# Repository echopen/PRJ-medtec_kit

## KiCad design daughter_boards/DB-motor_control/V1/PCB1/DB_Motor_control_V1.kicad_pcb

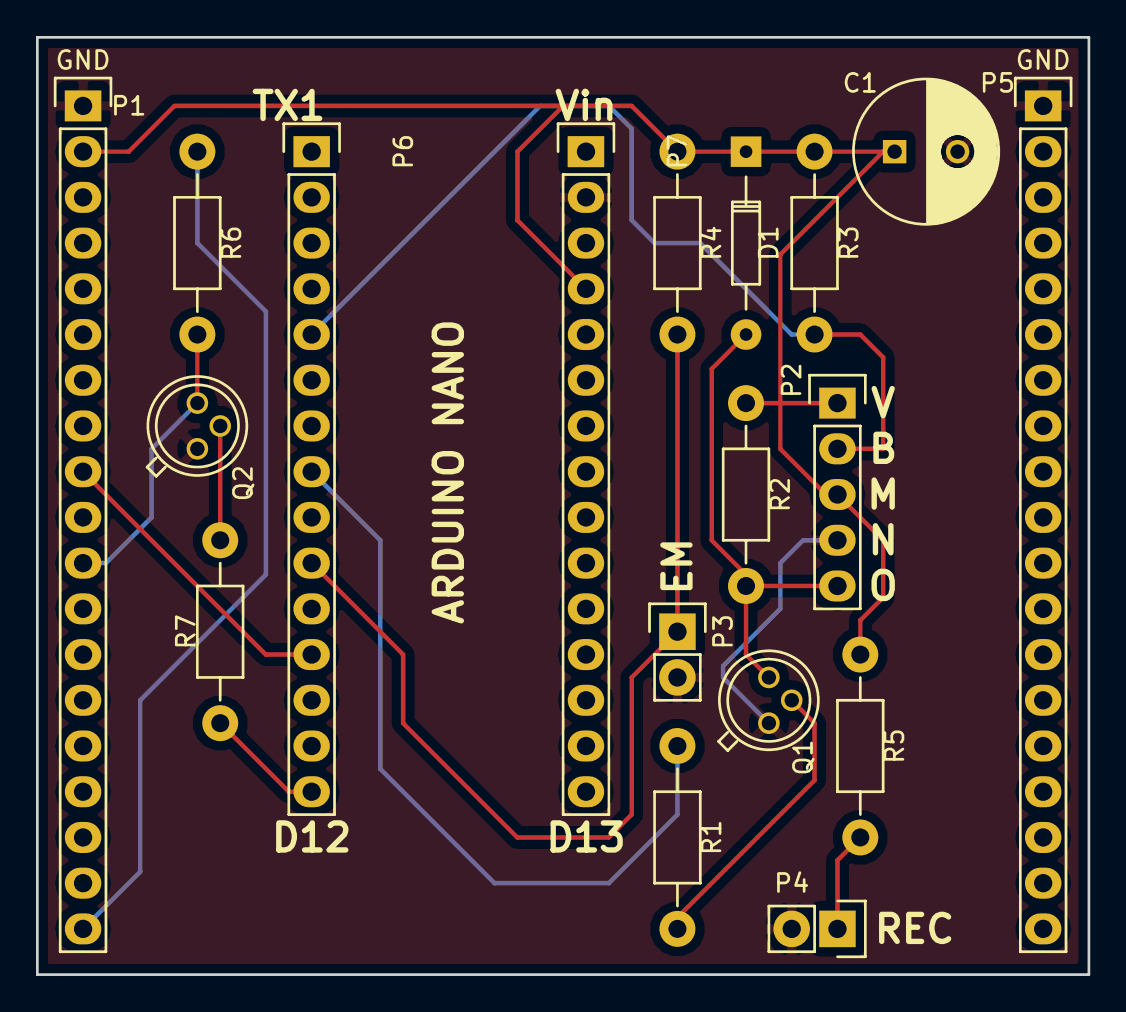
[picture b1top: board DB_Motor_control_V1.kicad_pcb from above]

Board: 2 copper layers, 58.4 x 52.1 mm, 18 parts (0 on the bottom side), 13 nets.

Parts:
C1: 10u; CP_TH_common
D1: 1N4001; Diode_DO-35_SOD27_Horizontal_RM10
P1, P5: CONN_01X19; Header_pin_1x19
P2: CONN_01X05; Socket_Strip_Straight_1x05
P3, P4: CONN_01X02; Socket_Strip_Straight_1x02
P6, P7: CONN_01X15; Socket_Strip_Straight_1x15
Q1: 2N2222; TO-18_3Pin
Q2: 2N2222; TO-18_TH_common
R1: 680; Resistor_Horizontal_RM10mm
R2: 1k; Resistor_Horizontal_RM10mm
R3: 33k; Resistor_Horizontal_RM10mm
R4: 2.2k; Resistor_Horizontal_RM10mm
R5: 330; Resistor_Horizontal_RM10mm
R6, R7: 1.5k; Resistor_TH_common

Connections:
GND: C1.2, P1.1, P2.4, P3.2, P4.2, P5.1, P7.2, Q1.1, Q2.1
unnamed: C1.1, D1.1, P1.2, P2.1, P2.3, P7.4, R2.1, R3.2, R4.1, R5.1
unnamed: D1.2, P2.5, Q1.3, R2.2
unnamed: P1.9, P6.12
unnamed: P1.11, Q2.3, R6.2
unnamed: P1.19, R6.1
unnamed: P2.2, P6.5, R3.1
unnamed: P3.1, P6.10, R4.2
unnamed: P4.1, R5.2
unnamed: P6.8, R1.2
unnamed: P6.15, R7.1
unnamed: Q1.2, R1.1
unnamed: Q2.2, R7.2

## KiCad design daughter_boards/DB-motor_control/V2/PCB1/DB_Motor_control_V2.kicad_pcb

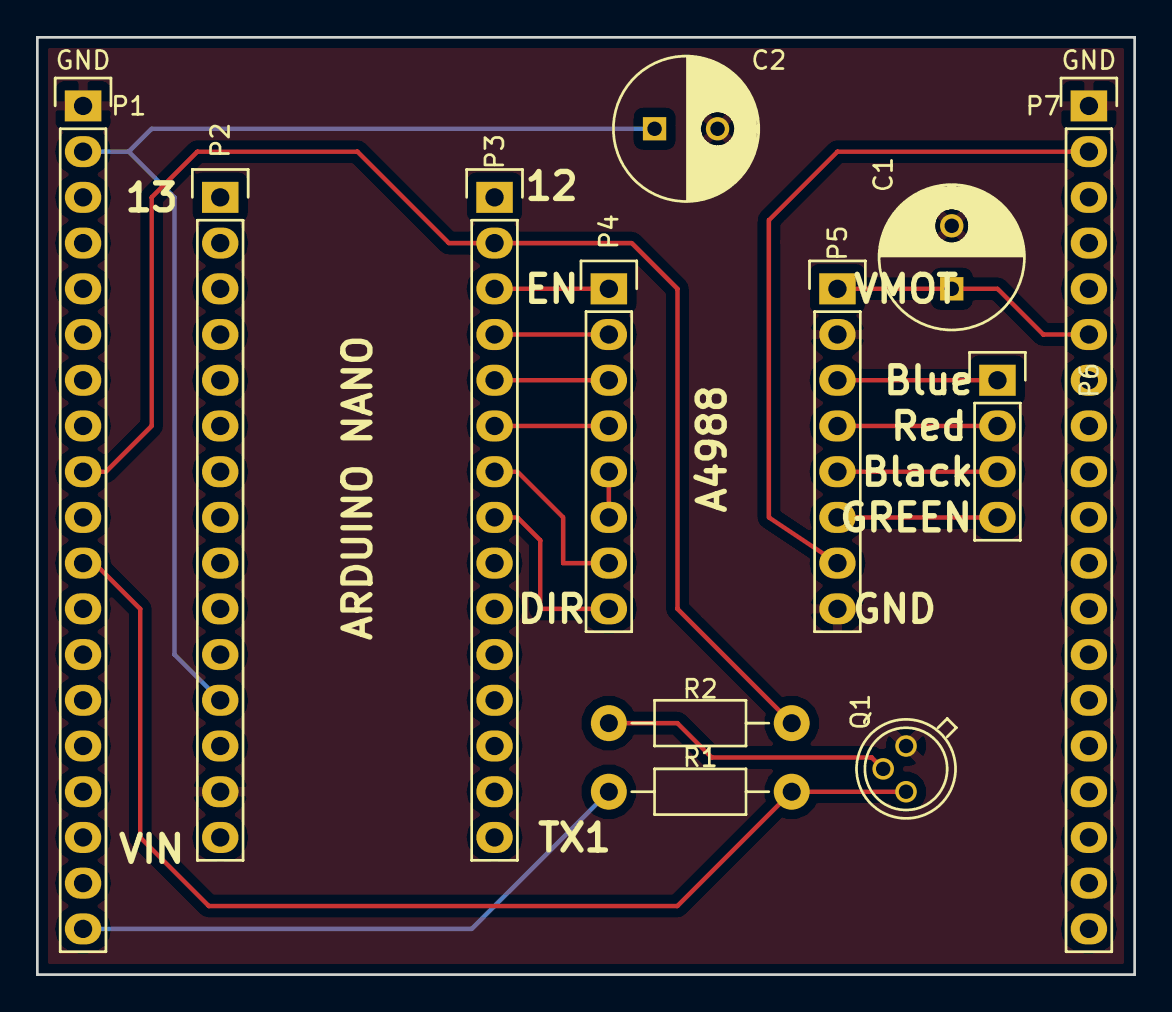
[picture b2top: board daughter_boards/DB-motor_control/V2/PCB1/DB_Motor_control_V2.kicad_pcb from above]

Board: 2 copper layers, 61.0 x 52.1 mm, 12 parts (0 on the bottom side), 19 nets.

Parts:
C1: 100u; CP_TH_common
C2: 10u; CP_TH_common
P1, P7: CONN_01X19; Header_pin_1x19
P2, P3: CONN_01X15; Socket_Strip_Straight_1x15
P4, P5: CONN_01X08; Socket_Strip_Straight_1x08
P6: CONN_01X04; Socket_Strip_Straight_1x04
Q1: 2N2222; TO-18_TH_common
R1, R2: 1.5k; Resistor_TH_common

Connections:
GND: C1.2, C2.2, P1.1, P2.14, P5.2, P5.8, P7.1, Q1.1
unnamed: C1.1, P5.1, P7.6
unnamed: C2.1, P1.2, P2.12
unnamed: P1.9, P3.2, R2.2
unnamed: P1.11, Q1.3, R1.2
unnamed: P1.19, R1.1
unnamed: P3.3, P4.1
unnamed: P3.4, P4.2
unnamed: P3.5, P4.3
unnamed: P3.6, P4.4
unnamed: P3.7, P4.7
unnamed: P3.8, P4.8
unnamed: P4.5, P4.6
unnamed: P5.3, P6.1
unnamed: P5.4, P6.2
unnamed: P5.5, P6.3
unnamed: P5.6, P6.4
unnamed: P5.7, P7.2
unnamed: Q1.2, R2.1

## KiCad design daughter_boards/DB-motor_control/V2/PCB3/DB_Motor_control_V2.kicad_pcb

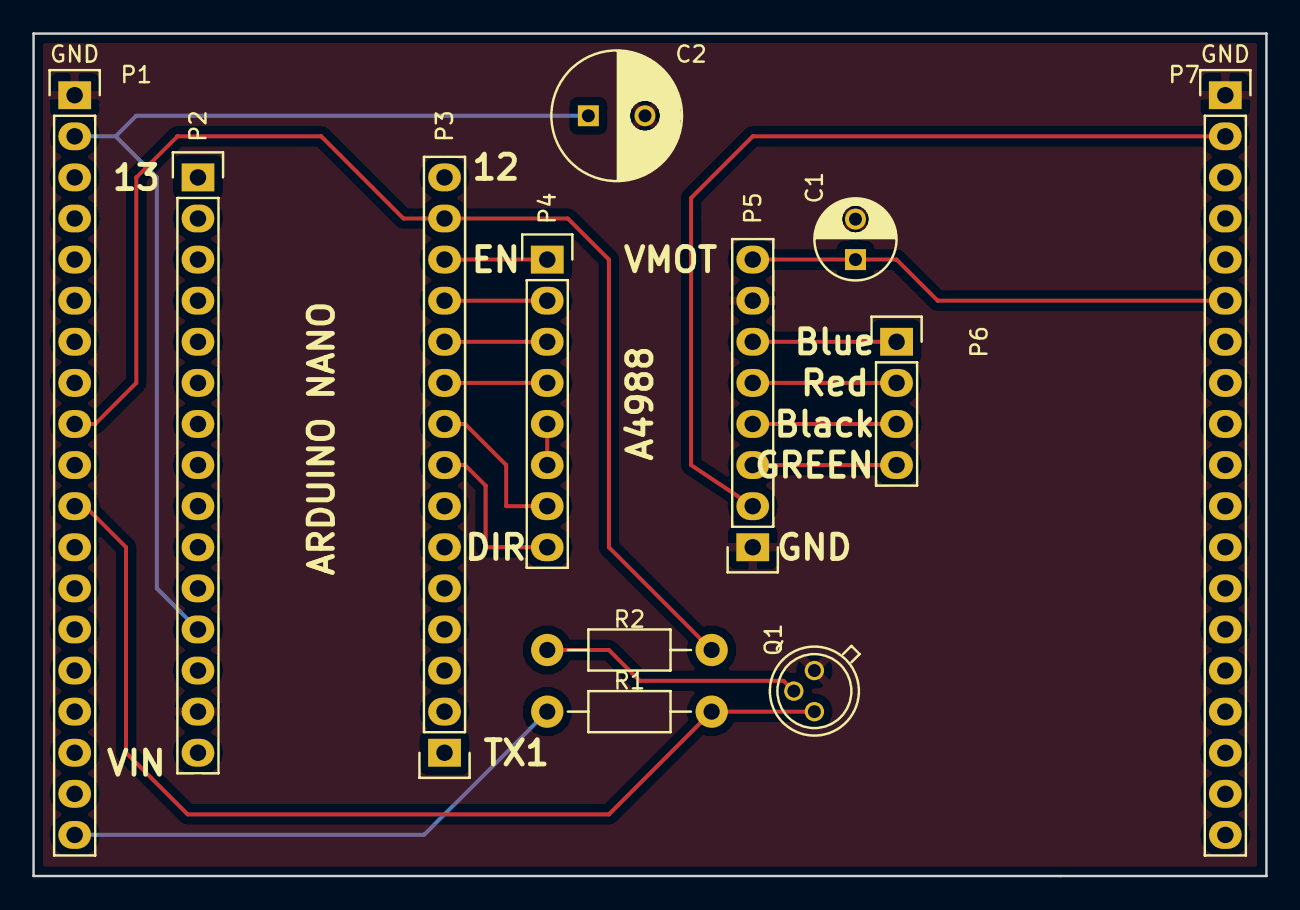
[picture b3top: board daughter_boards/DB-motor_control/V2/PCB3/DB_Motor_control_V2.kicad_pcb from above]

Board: 2 copper layers, 76.2 x 52.1 mm, 12 parts (0 on the bottom side), 19 nets.

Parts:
C1: 100u; C_Radial_D5_L6_P2.5
C2: 10u; CP_TH_common
P1, P7: CONN_01X19; Header_1x19
P2, P3: CONN_01X15; Socket_Strip_Straight_1x15
P4, P5: CONN_01X08; Socket_Strip_Straight_1x08
P6: CONN_01X04; Socket_Strip_Straight_1x04
Q1: 2N2222; TO-18_TH_common
R1, R2: 1.5k; Resistor_TH_common

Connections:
GND: C1.2, C2.2, P1.1, P2.14, P5.1, P5.7, P7.1, Q1.1
unnamed: C1.1, P5.8, P7.6
unnamed: C2.1, P1.2, P2.12
unnamed: P1.9, P3.14, R2.2
unnamed: P1.11, Q1.3, R1.2
unnamed: P1.19, R1.1
unnamed: P3.8, P4.8
unnamed: P3.9, P4.7
unnamed: P3.10, P4.4
unnamed: P3.11, P4.3
unnamed: P3.12, P4.2
unnamed: P3.13, P4.1
unnamed: P4.5, P4.6
unnamed: P5.2, P7.2
unnamed: P5.3, P6.4
unnamed: P5.4, P6.3
unnamed: P5.5, P6.2
unnamed: P5.6, P6.1
unnamed: Q1.2, R2.1

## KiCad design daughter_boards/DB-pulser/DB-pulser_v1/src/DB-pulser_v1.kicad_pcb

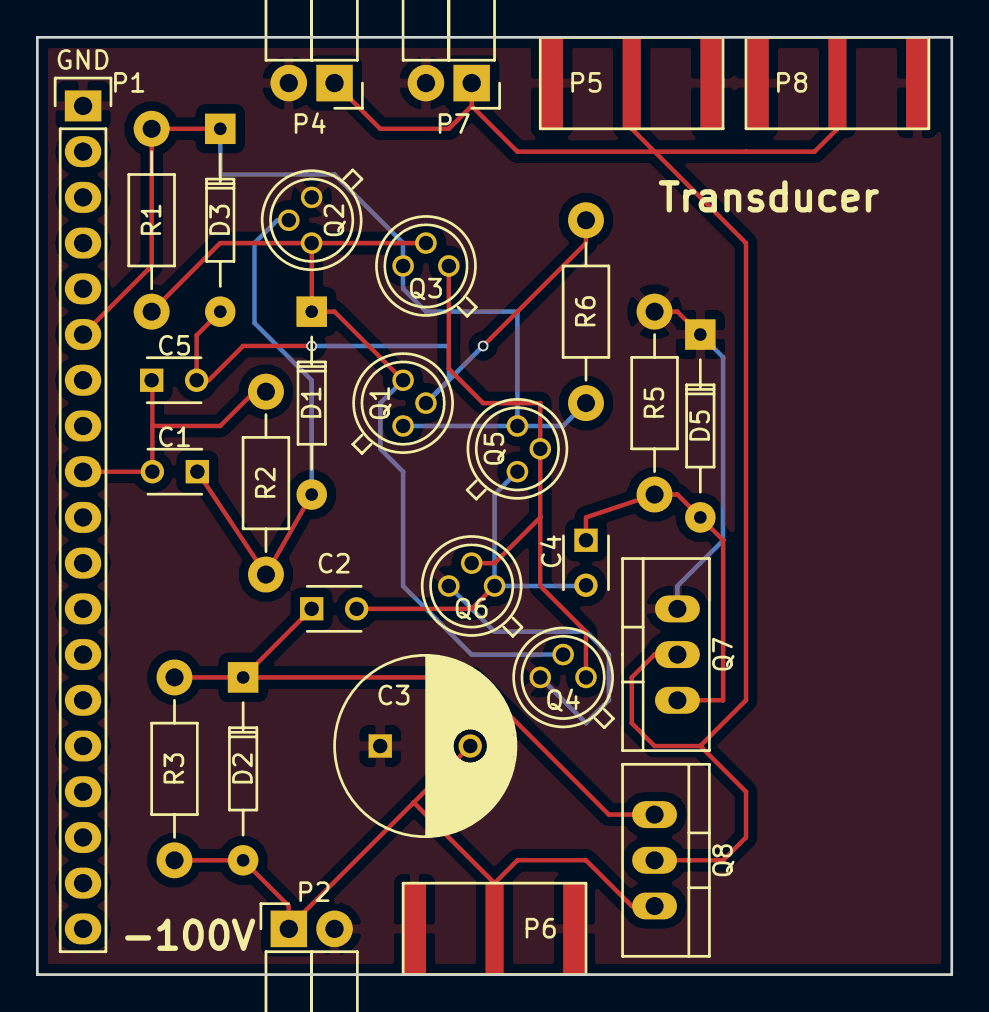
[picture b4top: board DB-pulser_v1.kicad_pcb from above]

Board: 2 copper layers, 50.8 x 52.1 mm, 29 parts (0 on the bottom side), 12 nets.

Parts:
C1: 100p; C_Disc_D3_P2.5
C2, C4: 100n; C_Disc_D3_P2.5
C3: 33u; C_Radial_D10_L13_P5
C5: 220p; C_Disc_D3_P2.5
D1: BAT48 0.6V; D_TH_common
D2, D5: BZD23-18; D_TH_common
D3: D1N4148; D_TH_common
P1: CONN_01X19; Header_pin_angled_1x19
P2, P4, P7: CONN_01X02; Socket_Strip_Angled_1x02
P5, P6, P8: SMA
Q1, Q4, Q6: 2N2907; TO-18_TH_common
Q2, Q3, Q5: 2N2222; TO-18_TH_common
Q7: IRF9610; TO-220_Neutral123_Vertical
Q8: IRF610; TO-220_Neutral123_Vertical
R1: 1k; Resistor_TH_common
R2: 22; Resistor_TH_common
R3, R5: 1M; Resistor_TH_common
R6: 100k; Resistor_TH_common

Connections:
GND: C3.1, D5.1, P1.1, P2.2, P4.2, P5.2, P6.2, P7.2, P8.2, Q2.1, Q4.3, Q6.3, Q7.3, R5.1
unnamed: C1.1, D1.2, Q2.2, R2.1
unnamed: C1.2, C5.1, P1.9, R2.2
unnamed: C2.1, D2.1, Q8.1, R3.1
unnamed: C2.2, C4.2, Q5.1, Q6.1
unnamed: C3.2, D2.2, P2.1, P6.1, Q8.3, R3.2
unnamed: C4.1, D5.2, Q7.1, R5.2
unnamed: C5.2, D3.2, Q1.2, R6.1
unnamed: D1.1, Q1.3, Q2.3, Q3.2, Q4.2, R1.2
unnamed: D3.1, P1.6, Q1.1, Q3.3, Q5.3, R1.1, R6.2
unnamed: P4.1, P5.1, P7.1, P8.1, Q7.2, Q8.2
unnamed: Q3.1, Q4.1, Q5.2, Q6.2
